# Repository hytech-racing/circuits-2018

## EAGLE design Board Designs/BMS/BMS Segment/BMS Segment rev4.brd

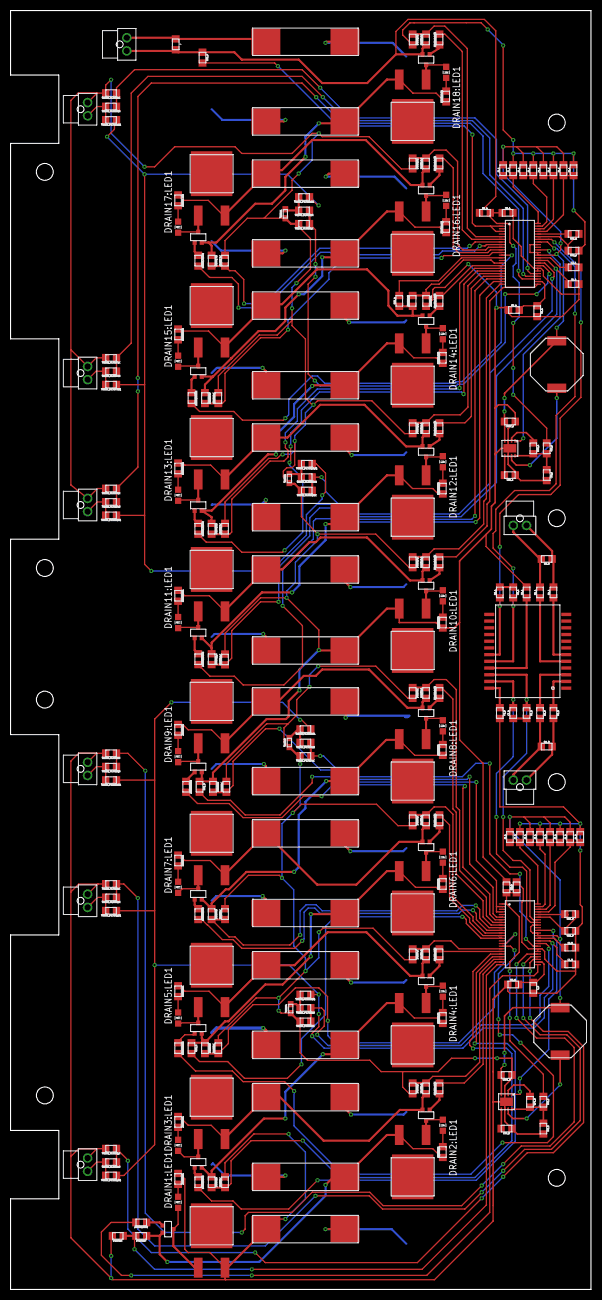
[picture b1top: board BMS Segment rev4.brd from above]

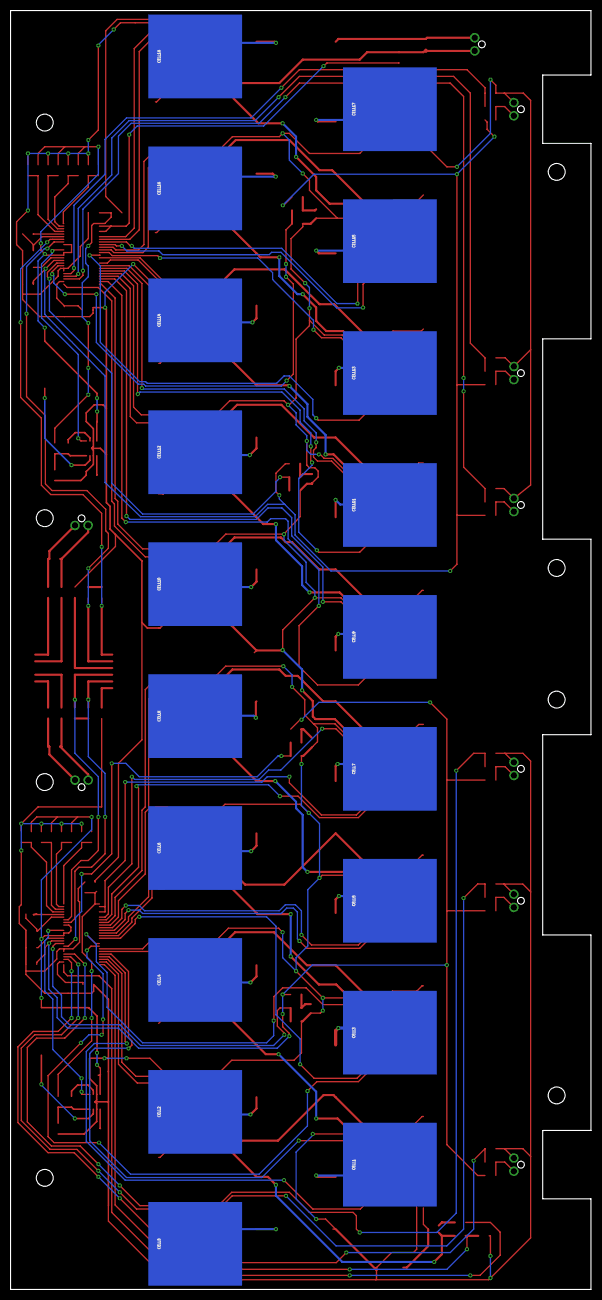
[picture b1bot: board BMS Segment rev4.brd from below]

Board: 2 copper layers, 110.0 x 242.3 mm, 273 parts (19 on the bottom side), 201 nets.

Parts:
AMS_TEST_PORT1: CONNECTOR-2NANO-FIT_VERTICAL-2; NANO-FIT_VERTICAL-2
BUCK_CONV_A: ADP2360; LFCSP-8
BUCK_CONV_B: ADP2360; LFCSP-8
C1_A, C1_B, C2_A, C2_B: 1uF; 0805
C3_A, C3_B: 15pF; 0805
C4_A, C4_B, C5_A: 10nF; 0805
C6_A, C6_B: 0.1uF; 0805
CELL0, CELL1, CELL2, CELL3, CELL4, CELL5, CELL6, CELL7, CELL8, CELL9, CELL10, CELL11, CELL12, CELL13, CELL14, CELL15, CELL16, CELL17, CELL18: BATTERY_SPRING_KEYSTONE5222; KEYSTONE5222
CIN_A: 4.7uF; 0805
CIN_B: 4.7uF; 0805
COUT_A: 22uF; 0805
COUT_B: 22uF; 0805
CSS_A: 2.2nF; 0805
CSS_B: 2.2nF; 0805
C_5: 10nF; 0805
DRAIN1:C, DRAIN2:C, DRAIN3:C, DRAIN4:C, DRAIN5:C, DRAIN6:C, DRAIN7:C, DRAIN8:C, DRAIN9:C, DRAIN10:C, DRAIN11:C, DRAIN12:C, DRAIN13:C, DRAIN14:C, DRAIN15:C, DRAIN16:C, DRAIN17:C, DRAIN18:C: 10nF; 0805
DRAIN1:DISCHARGE, DRAIN2:DISCHARGE, DRAIN3:DISCHARGE, DRAIN4:DISCHARGE, DRAIN5:DISCHARGE, DRAIN6:DISCHARGE, DRAIN7:DISCHARGE, DRAIN8:DISCHARGE, DRAIN9:DISCHARGE, DRAIN10:DISCHARGE, DRAIN11:DISCHARGE, DRAIN12:DISCHARGE, DRAIN13:DISCHARGE, DRAIN14:DISCHARGE, DRAIN15:DISCHARGE, DRAIN16:DISCHARGE, DRAIN17:DISCHARGE, DRAIN18:DISCHARGE: 5Ω; PWR163
DRAIN1:GATE, DRAIN2:GATE, DRAIN3:GATE, DRAIN4:GATE, DRAIN5:GATE, DRAIN6:GATE, DRAIN7:GATE, DRAIN8:GATE, DRAIN9:GATE, DRAIN10:GATE, DRAIN11:GATE, DRAIN12:GATE, DRAIN13:GATE, DRAIN14:GATE, DRAIN15:GATE, DRAIN16:GATE, DRAIN17:GATE, DRAIN18:GATE: 3.3kΩ; 0805
DRAIN1:LED1, DRAIN2:LED1, DRAIN3:LED1, DRAIN4:LED1, DRAIN5:LED1, DRAIN6:LED1, DRAIN7:LED1, DRAIN8:LED1, DRAIN9:LED1, DRAIN10:LED1, DRAIN11:LED1, DRAIN12:LED1, DRAIN13:LED1, DRAIN14:LED1, DRAIN15:LED1, DRAIN16:LED1, DRAIN17:LED1, DRAIN18:LED1: RED; LED-805
DRAIN1:PFET, DRAIN2:PFET, DRAIN3:PFET, DRAIN4:PFET, DRAIN5:PFET, DRAIN6:PFET, DRAIN7:PFET, DRAIN8:PFET, DRAIN9:PFET, DRAIN10:PFET, DRAIN11:PFET, DRAIN12:PFET, DRAIN13:PFET, DRAIN14:PFET, DRAIN15:PFET, DRAIN16:PFET, DRAIN17:PFET, DRAIN18:PFET: P-CHANNEL_MOSFET_DMP3099L-7; SOT23
DRAIN1:R, DRAIN2:R, DRAIN3:R, DRAIN4:R, DRAIN5:R, DRAIN6:R, DRAIN7:R, DRAIN8:R, DRAIN9:R, DRAIN10:R, DRAIN11:R, DRAIN12:R, DRAIN13:R, DRAIN14:R, DRAIN15:R, DRAIN16:R, DRAIN17:R, DRAIN18:R: 100Ω; 0805
DRAIN1:R1, DRAIN2:R1, DRAIN3:R1, DRAIN4:R1, DRAIN5:R1, DRAIN6:R1, DRAIN7:R1, DRAIN8:R1, DRAIN9:R1, DRAIN10:R1, DRAIN11:R1, DRAIN12:R1, DRAIN13:R1, DRAIN14:R1, DRAIN15:R1, DRAIN16:R1, DRAIN17:R1, DRAIN18:R1: 150; 0805
F0, F1, F2, F3, F4, F5, F6, F7, F8, F9, F10, F11, F12, F13, F14, F15, F16, F17, F18: 0001.2704.11; 5X20MM_FUSE
ISOSPI_A: CONNECTOR-2NANO-FIT_VERTICAL-2; NANO-FIT_VERTICAL-2
ISOSPI_B: CONNECTOR-2NANO-FIT_VERTICAL-2; NANO-FIT_VERTICAL-2
J, J1_A, J1_B, J2_A, J2_B, J3_A, J3_B, J4_A, J4_B, J5_A, J5_B, J6_A, J6_B, J7_A, J7_B, J8_A, J8_B: 0805
L1_A, L1_B: 330uH; SRU1048
R1_A, R1_B, R2_A, R2_B: 100Ω; 0805
R3_A, R3_B: 402Ω; 0805
R4_A, R4_B, R5_A, R5_B: 22Ω; 0805
RB1_A, RB1_B: 1.2kΩ; 0805
RB2_A, RB2_B: 800Ω; 0805
RIN_A: 1kΩ; 0805
RIN_B: 1kΩ; 0805
RM_A: 100Ω; 0805
RM_B: 100Ω; 0805
RPG_A: 10MΩ; 0805
RPG_B: 10MΩ; 0805
RU1_A, RU1_B, RU2_A, RU2_B: 100Ω; 0805
THERM1, THERM2, THERM3, THERM4: 10kΩ; 0603
THERM1A, THERM1_B: Th1; NANO-FIT_VERTICAL-2
THERM2A, THERM2_B: Th2; NANO-FIT_VERTICAL-2
THERM3A, THERM3_B: Th3; NANO-FIT_VERTICAL-2
THERM_FILTER1:C, THERM_FILTER2:C, THERM_FILTER3:C, THERM_FILTER4:C, THERM_FILTER5:C, THERM_FILTER6:C, THERM_FILTER7:C, THERM_FILTER8:C, THERM_FILTER9:C, THERM_FILTER10:C: 10nF; 0805
THERM_FILTER1:R, THERM_FILTER2:R, THERM_FILTER3:R, THERM_FILTER4:R, THERM_FILTER5:R, THERM_FILTER6:R, THERM_FILTER7:R, THERM_FILTER8:R, THERM_FILTER9:R, THERM_FILTER10:R: 100Ω; 0805
THERM_FILTER1:R1, THERM_FILTER2:R1, THERM_FILTER3:R1, THERM_FILTER4:R1, THERM_FILTER5:R1, THERM_FILTER6:R1, THERM_FILTER7:R1, THERM_FILTER8:R1, THERM_FILTER9:R1, THERM_FILTER10:R1: 10kΩ; 0805
TRANSFORMER: SM51589PEL
U$1, U$2: LTC6804-2; LTC6804

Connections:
C0_A: C5_A.1, R2_A.2, U$1.26
C0_B: C_5.1, R2_B.2, U$2.26
C1_A: DRAIN10:C.1, DRAIN10:R.2, U$1.24
C1_B: DRAIN1:C.1, DRAIN1:R.2, U$2.24
C2_A: DRAIN11:C.1, DRAIN11:R.2, U$1.22
C2_B: DRAIN2:C.1, DRAIN2:R.2, U$2.22
C3_A: DRAIN12:C.1, DRAIN12:R.2, U$1.20
C3_B: DRAIN3:C.1, DRAIN3:R.2, U$2.20
C4_A: DRAIN13:C.1, DRAIN13:R.2, U$1.18
C4_B: DRAIN4:C.1, DRAIN4:R.2, U$2.18
C5_A: DRAIN14:C.1, DRAIN14:R.2, U$1.16
C5_B: DRAIN5:C.1, DRAIN5:R.2, U$2.16
C7_A: DRAIN15:C.1, DRAIN15:R.2, U$1.12
C7_B: DRAIN6:C.1, DRAIN6:R.2, U$2.12
C8_A: DRAIN16:C.1, DRAIN16:R.2, U$1.10
C8_B: DRAIN7:C.1, DRAIN7:R.2, U$2.10
C9_A: DRAIN17:C.1, DRAIN17:R.2, U$1.8
C9_B: DRAIN8:C.1, DRAIN8:R.2, U$2.8
C10_A: DRAIN18:C.1, DRAIN18:R.2, U$1.6
C10_B: DRAIN9:C.1, DRAIN9:R.2, U$2.6
CC0: CELL0.P$1, F0.P$1
CC1: CELL1.P$1, F1.P$1
CC2: CELL2.P$1, F2.P$1
CC3: CELL3.P$1, F3.P$1
CC4: CELL4.P$1, F4.P$1
CC5: CELL5.P$1, F5.P$1
CC6: CELL6.P$1, F6.P$1
CC7: CELL7.P$1, F7.P$1
CC8: CELL8.P$1, F8.P$1
CC9: CELL9.P$1, F9.P$1
CC10: CELL10.P$1, F10.P$1
CC11: CELL11.P$1, F11.P$1
CC12: CELL12.P$1, F12.P$1
CC13: CELL13.P$1, F13.P$1
CC14: CELL14.P$1, F14.P$1
CC15: CELL15.P$1, F15.P$1
CC16: CELL16.P$1, F16.P$1
CC17: CELL17.P$1, F17.P$1
CC18: CELL18.P$1, F18.P$1
DRAIN1:GATE: DRAIN1:GATE.1, DRAIN1:PFET.1
DRAIN1:N$1: DRAIN1:DISCHARGE.1, DRAIN1:LED1.A, DRAIN1:PFET.3
DRAIN1:N$2: DRAIN1:LED1.C, DRAIN1:R1.2
DRAIN2:GATE: DRAIN2:GATE.1, DRAIN2:PFET.1
DRAIN2:N$1: DRAIN2:DISCHARGE.1, DRAIN2:LED1.A, DRAIN2:PFET.3
DRAIN2:N$2: DRAIN2:LED1.C, DRAIN2:R1.2
DRAIN3:GATE: DRAIN3:GATE.1, DRAIN3:PFET.1
DRAIN3:N$1: DRAIN3:DISCHARGE.1, DRAIN3:LED1.A, DRAIN3:PFET.3
DRAIN3:N$2: DRAIN3:LED1.C, DRAIN3:R1.2
DRAIN4:GATE: DRAIN4:GATE.1, DRAIN4:PFET.1
DRAIN4:N$1: DRAIN4:DISCHARGE.1, DRAIN4:LED1.A, DRAIN4:PFET.3
DRAIN4:N$2: DRAIN4:LED1.C, DRAIN4:R1.2
DRAIN5:GATE: DRAIN5:GATE.1, DRAIN5:PFET.1
DRAIN5:N$1: DRAIN5:DISCHARGE.1, DRAIN5:LED1.A, DRAIN5:PFET.3
DRAIN5:N$2: DRAIN5:LED1.C, DRAIN5:R1.2
DRAIN6:GATE: DRAIN6:GATE.1, DRAIN6:PFET.1
DRAIN6:N$1: DRAIN6:DISCHARGE.1, DRAIN6:LED1.A, DRAIN6:PFET.3
DRAIN6:N$2: DRAIN6:LED1.C, DRAIN6:R1.2
DRAIN7:GATE: DRAIN7:GATE.1, DRAIN7:PFET.1
DRAIN7:N$1: DRAIN7:DISCHARGE.1, DRAIN7:LED1.A, DRAIN7:PFET.3
DRAIN7:N$2: DRAIN7:LED1.C, DRAIN7:R1.2
DRAIN8:GATE: DRAIN8:GATE.1, DRAIN8:PFET.1
DRAIN8:N$1: DRAIN8:DISCHARGE.1, DRAIN8:LED1.A, DRAIN8:PFET.3
DRAIN8:N$2: DRAIN8:LED1.C, DRAIN8:R1.2
DRAIN9:GATE: DRAIN9:GATE.1, DRAIN9:PFET.1
DRAIN9:N$1: DRAIN9:DISCHARGE.1, DRAIN9:LED1.A, DRAIN9:PFET.3
DRAIN9:N$2: DRAIN9:LED1.C, DRAIN9:R1.2
DRAIN10:GATE: DRAIN10:GATE.1, DRAIN10:PFET.1
DRAIN10:N$1: DRAIN10:DISCHARGE.1, DRAIN10:LED1.A, DRAIN10:PFET.3
DRAIN10:N$2: DRAIN10:LED1.C, DRAIN10:R1.2
DRAIN11:GATE: DRAIN11:GATE.1, DRAIN11:PFET.1
DRAIN11:N$1: DRAIN11:DISCHARGE.1, DRAIN11:LED1.A, DRAIN11:PFET.3
DRAIN11:N$2: DRAIN11:LED1.C, DRAIN11:R1.2
DRAIN12:GATE: DRAIN12:GATE.1, DRAIN12:PFET.1
DRAIN12:N$1: DRAIN12:DISCHARGE.1, DRAIN12:LED1.A, DRAIN12:PFET.3
DRAIN12:N$2: DRAIN12:LED1.C, DRAIN12:R1.2
DRAIN13:GATE: DRAIN13:GATE.1, DRAIN13:PFET.1
DRAIN13:N$1: DRAIN13:DISCHARGE.1, DRAIN13:LED1.A, DRAIN13:PFET.3
DRAIN13:N$2: DRAIN13:LED1.C, DRAIN13:R1.2
DRAIN14:GATE: DRAIN14:GATE.1, DRAIN14:PFET.1
DRAIN14:N$1: DRAIN14:DISCHARGE.1, DRAIN14:LED1.A, DRAIN14:PFET.3
DRAIN14:N$2: DRAIN14:LED1.C, DRAIN14:R1.2
DRAIN15:GATE: DRAIN15:GATE.1, DRAIN15:PFET.1
DRAIN15:N$1: DRAIN15:DISCHARGE.1, DRAIN15:LED1.A, DRAIN15:PFET.3
DRAIN15:N$2: DRAIN15:LED1.C, DRAIN15:R1.2
DRAIN16:GATE: DRAIN16:GATE.1, DRAIN16:PFET.1
DRAIN16:N$1: DRAIN16:DISCHARGE.1, DRAIN16:LED1.A, DRAIN16:PFET.3
DRAIN16:N$2: DRAIN16:LED1.C, DRAIN16:R1.2
DRAIN17:GATE: DRAIN17:GATE.1, DRAIN17:PFET.1
DRAIN17:N$1: DRAIN17:DISCHARGE.1, DRAIN17:LED1.A, DRAIN17:PFET.3
DRAIN17:N$2: DRAIN17:LED1.C, DRAIN17:R1.2
DRAIN18:GATE: DRAIN18:GATE.1, DRAIN18:PFET.1
DRAIN18:N$1: DRAIN18:DISCHARGE.1, DRAIN18:LED1.A, DRAIN18:PFET.3
DRAIN18:N$2: DRAIN18:LED1.C, DRAIN18:R1.2
DRIVE_A: BUCK_CONV_A.1, U$1.38
DRIVE_B: BUCK_CONV_B.1, U$2.38
GPIO1_A: THERM_FILTER6:C.1, THERM_FILTER6:R.1, U$1.27
GPIO1_B: THERM_FILTER1:C.1, THERM_FILTER1:R.1, U$2.27
GPIO2_A: THERM_FILTER7:C.1, THERM_FILTER7:R.1, U$1.28
GPIO2_B: THERM_FILTER2:C.1, THERM_FILTER2:R.1, U$2.28
GPIO3_A: THERM_FILTER8:C.1, THERM_FILTER8:R.1, U$1.29
GPIO3_B: THERM_FILTER3:C.1, THERM_FILTER3:R.1, U$2.29
GPIO4_A: THERM_FILTER9:C.1, THERM_FILTER9:R.1, U$1.32
GPIO4_B: THERM_FILTER4:C.1, THERM_FILTER4:R.1, U$2.32
GPIO5_A: THERM_FILTER10:C.1, THERM_FILTER10:R.1, U$1.33
GPIO5_B: THERM_FILTER5:C.1, THERM_FILTER5:R.1, U$2.33
IM_A: C3_A.2, TRANSFORMER.20, U$1.41
IM_B: C3_B.2, TRANSFORMER.23, U$2.41
IP_A: R3_A.1, TRANSFORMER.19, U$1.42
IP_B: R3_B.1, TRANSFORMER.22, U$2.42
ISOSPI-M_A: ISOSPI_A.P$2, R5_A.2, RM_A.2
ISOSPI-M_B: ISOSPI_B.P$2, R5_B.2, RM_B.2
ISOSPI-P_A: ISOSPI_A.P$1, R4_A.2, RM_A.1
ISOSPI-P_B: ISOSPI_B.P$1, R4_B.2, RM_B.1
unnamed: C4_B.1, TRANSFORMER.24
unnamed: RB1_B.2, U$2.44
unnamed: THERM1_B.P$2, THERM_FILTER1:R.2, THERM_FILTER1:R1.2
unnamed: RB1_B.1, RB2_B.2, U$2.43
unnamed: R4_B.1, TRANSFORMER.3
unnamed: RB1_A.2, U$1.44
unnamed: R5_B.1, TRANSFORMER.2
unnamed: J7_B.1, J8_B.1, U$2.48
unnamed: J5_B.1, J6_B.1, U$2.47
unnamed: C3_B.1, R3_B.2
unnamed: BUCK_CONV_B.8, CIN_B.1, RIN_B.2, RPG_B.2
unnamed: BUCK_CONV_B.2, RPG_B.1
unnamed: J3_B.1, J4_B.1, U$2.46
unnamed: BUCK_CONV_B.5, CSS_B.2
unnamed: BUCK_CONV_B.7, L1_B.1
unnamed: J1_B.1, J2_B.1, U$2.45
unnamed: THERM4.2, THERM_FILTER5:R.2, THERM_FILTER5:R1.2
unnamed: THERM2_B.P$2, THERM_FILTER2:R.2, THERM_FILTER2:R1.2
unnamed: THERM3.2, THERM_FILTER4:R.2, THERM_FILTER4:R1.2
unnamed: RB1_A.1, RB2_A.2, U$1.43
unnamed: C4_A.1, TRANSFORMER.21
unnamed: R4_A.1, TRANSFORMER.6
unnamed: R5_A.1, TRANSFORMER.5
unnamed: C3_A.1, R3_A.2
unnamed: BUCK_CONV_A.8, CIN_A.1, RIN_A.2, RPG_A.2
unnamed: THERM3_B.P$2, THERM_FILTER3:R.2, THERM_FILTER3:R1.2
unnamed: BUCK_CONV_A.2, RPG_A.1
unnamed: BUCK_CONV_A.5, CSS_A.2
unnamed: BUCK_CONV_A.7, L1_A.1
unnamed: J7_A.1, J8_A.1, U$1.48
unnamed: J5_A.1, J6_A.1, U$1.47
unnamed: J3_A.1, J4_A.1, U$1.46
unnamed: J1_A.1, J2_A.1, U$1.45
unnamed: THERM1.2, THERM_FILTER9:R.2, THERM_FILTER9:R1.2
unnamed: THERM3A.P$2, THERM_FILTER8:R.2, THERM_FILTER8:R1.2
unnamed: THERM2.2, THERM_FILTER10:R.2, THERM_FILTER10:R1.2
unnamed: THERM2A.P$2, THERM_FILTER7:R.2, THERM_FILTER7:R1.2
unnamed: THERM1A.P$2, THERM_FILTER6:R.2, THERM_FILTER6:R1.2
S1_A: DRAIN10:GATE.2, U$1.25
S1_B: DRAIN1:GATE.2, U$2.25
S2_A: DRAIN11:GATE.2, U$1.23
S2_B: DRAIN2:GATE.2, U$2.23
S3_A: DRAIN12:GATE.2, U$1.21
S3_B: DRAIN3:GATE.2, U$2.21
S4_A: DRAIN13:GATE.2, U$1.19
S4_B: DRAIN4:GATE.2, U$2.19
S5_A: DRAIN14:GATE.2, U$1.17
S5_B: DRAIN5:GATE.2, U$2.17
S7_A: DRAIN15:GATE.2, U$1.13
S7_B: DRAIN6:GATE.2, U$2.13
S8_A: DRAIN16:GATE.2, U$1.11
S8_B: DRAIN7:GATE.2, U$2.11
S9_A: DRAIN17:GATE.2, U$1.9
S9_B: DRAIN8:GATE.2, U$2.9
S10_A: DRAIN18:GATE.2, U$1.7
S10_B: DRAIN9:GATE.2, U$2.7
SENSE1: DRAIN1:PFET.2, DRAIN1:R.1, DRAIN2:DISCHARGE.2, DRAIN2:R1.1, F1.P$2
SENSE2: DRAIN2:PFET.2, DRAIN2:R.1, DRAIN3:DISCHARGE.2, DRAIN3:R1.1, F2.P$2
SENSE3: DRAIN3:PFET.2, DRAIN3:R.1, DRAIN4:DISCHARGE.2, DRAIN4:R1.1, F3.P$2
SENSE4: DRAIN4:PFET.2, DRAIN4:R.1, DRAIN5:DISCHARGE.2, DRAIN5:R1.1, F4.P$2
SENSE5: DRAIN5:PFET.2, DRAIN5:R.1, DRAIN6:DISCHARGE.2, DRAIN6:R1.1, F5.P$2, RU2_B.1
SENSE6: DRAIN6:PFET.2, DRAIN6:R.1, DRAIN7:DISCHARGE.2, DRAIN7:R1.1, F6.P$2
SENSE7: DRAIN7:PFET.2, DRAIN7:R.1, DRAIN8:DISCHARGE.2, DRAIN8:R1.1, F7.P$2
SENSE8: DRAIN8:PFET.2, DRAIN8:R.1, DRAIN9:DISCHARGE.2, DRAIN9:R1.1, F8.P$2
SENSE10: DRAIN10:PFET.2, DRAIN10:R.1, DRAIN11:DISCHARGE.2, DRAIN11:R1.1, F10.P$2
SENSE11: DRAIN11:PFET.2, DRAIN11:R.1, DRAIN12:DISCHARGE.2, DRAIN12:R1.1, F11.P$2
SENSE12: DRAIN12:PFET.2, DRAIN12:R.1, DRAIN13:DISCHARGE.2, DRAIN13:R1.1, F12.P$2
SENSE13: DRAIN13:PFET.2, DRAIN13:R.1, DRAIN14:DISCHARGE.2, DRAIN14:R1.1, F13.P$2
SENSE14: DRAIN14:PFET.2, DRAIN14:R.1, DRAIN15:DISCHARGE.2, DRAIN15:R1.1, F14.P$2, RU2_A.1
SENSE15: DRAIN15:PFET.2, DRAIN15:R.1, DRAIN16:DISCHARGE.2, DRAIN16:R1.1, F15.P$2
SENSE16: DRAIN16:PFET.2, DRAIN16:R.1, DRAIN17:DISCHARGE.2, DRAIN17:R1.1, F16.P$2
SENSE17: DRAIN17:PFET.2, DRAIN17:R.1, DRAIN18:DISCHARGE.2, DRAIN18:R1.1, F17.P$2
SENSE18: AMS_TEST_PORT1.P$2, DRAIN18:PFET.2, DRAIN18:R.1, J.2, R1_A.1, RU1_A.1
SENSE18_J: AMS_TEST_PORT1.P$1, F18.P$2, J.1
UNUSED1_A: RU1_A.2, U$1.2, U$1.4
UNUSED1_B: RU1_B.2, U$2.2, U$2.4
UNUSED2_A: RU2_A.2, U$1.14
UNUSED2_B: RU2_B.2, U$2.14
V+_A: C6_A.1, R1_A.2, RIN_A.1, U$1.1
V+_B: C6_B.1, R1_B.2, RIN_B.1, U$2.1
V-_A: BUCK_CONV_A.3, BUCK_CONV_A.6, BUCK_CONV_A.PAD, C1_A.2, C2_A.2, C4_A.2, C5_A.2, C6_A.2, CIN_A.2, COUT_A.1, CSS_A.1, DRAIN9:PFET.2, DRAIN9:R.1, DRAIN10:C.2, DRAIN10:DISCHARGE.2, DRAIN10:R1.1, DRAIN11:C.2, DRAIN12:C.2, DRAIN13:C.2, DRAIN14:C.2, DRAIN15:C.2, DRAIN16:C.2, DRAIN17:C.2, DRAIN18:C.2, F9.P$2, J1_A.2, J3_A.2, J5_A.2, J7_A.2, R1_B.1, R2_A.1, RB2_A.1, RU1_B.1, THERM1.1, THERM1A.P$1, THERM2.1, THERM2A.P$1, THERM3A.P$1, THERM_FILTER6:C.2, THERM_FILTER7:C.2, THERM_FILTER8:C.2, THERM_FILTER9:C.2, THERM_FILTER10:C.2, U$1.30, U$1.31
V-_B: BUCK_CONV_B.3, BUCK_CONV_B.6, BUCK_CONV_B.PAD, C1_B.2, C2_B.2, C4_B.2, C6_B.2, CIN_B.2, COUT_B.1, CSS_B.1, C_5.2, DRAIN1:C.2, DRAIN1:DISCHARGE.2, DRAIN1:R1.1, DRAIN2:C.2, DRAIN3:C.2, DRAIN4:C.2, DRAIN5:C.2, DRAIN6:C.2, DRAIN7:C.2, DRAIN8:C.2, DRAIN9:C.2, F0.P$2, J1_B.2, J3_B.2, J5_B.2, J7_B.2, R2_B.1, RB2_B.1, THERM1_B.P$1, THERM2_B.P$1, THERM3.1, THERM3_B.P$1, THERM4.1, THERM_FILTER1:C.2, THERM_FILTER2:C.2, THERM_FILTER3:C.2, THERM_FILTER4:C.2, THERM_FILTER5:C.2, U$2.30, U$2.31
VREF1_A: C2_A.1, U$1.35
VREF1_B: C2_B.1, U$2.35
VREF2_A: C1_A.1, THERM_FILTER6:R1.1, THERM_FILTER7:R1.1, THERM_FILTER8:R1.1, THERM_FILTER9:R1.1, THERM_FILTER10:R1.1, U$1.34
VREF2_B: C1_B.1, THERM_FILTER1:R1.1, THERM_FILTER2:R1.1, THERM_FILTER3:R1.1, THERM_FILTER4:R1.1, THERM_FILTER5:R1.1, U$2.34
VREG_A: BUCK_CONV_A.4, COUT_A.2, J2_A.2, J4_A.2, J6_A.2, J8_A.2, L1_A.2, U$1.36, U$1.37, U$1.40
VREG_B: BUCK_CONV_B.4, COUT_B.2, J2_B.2, J4_B.2, J6_B.2, J8_B.2, L1_B.2, U$2.36, U$2.37, U$2.40

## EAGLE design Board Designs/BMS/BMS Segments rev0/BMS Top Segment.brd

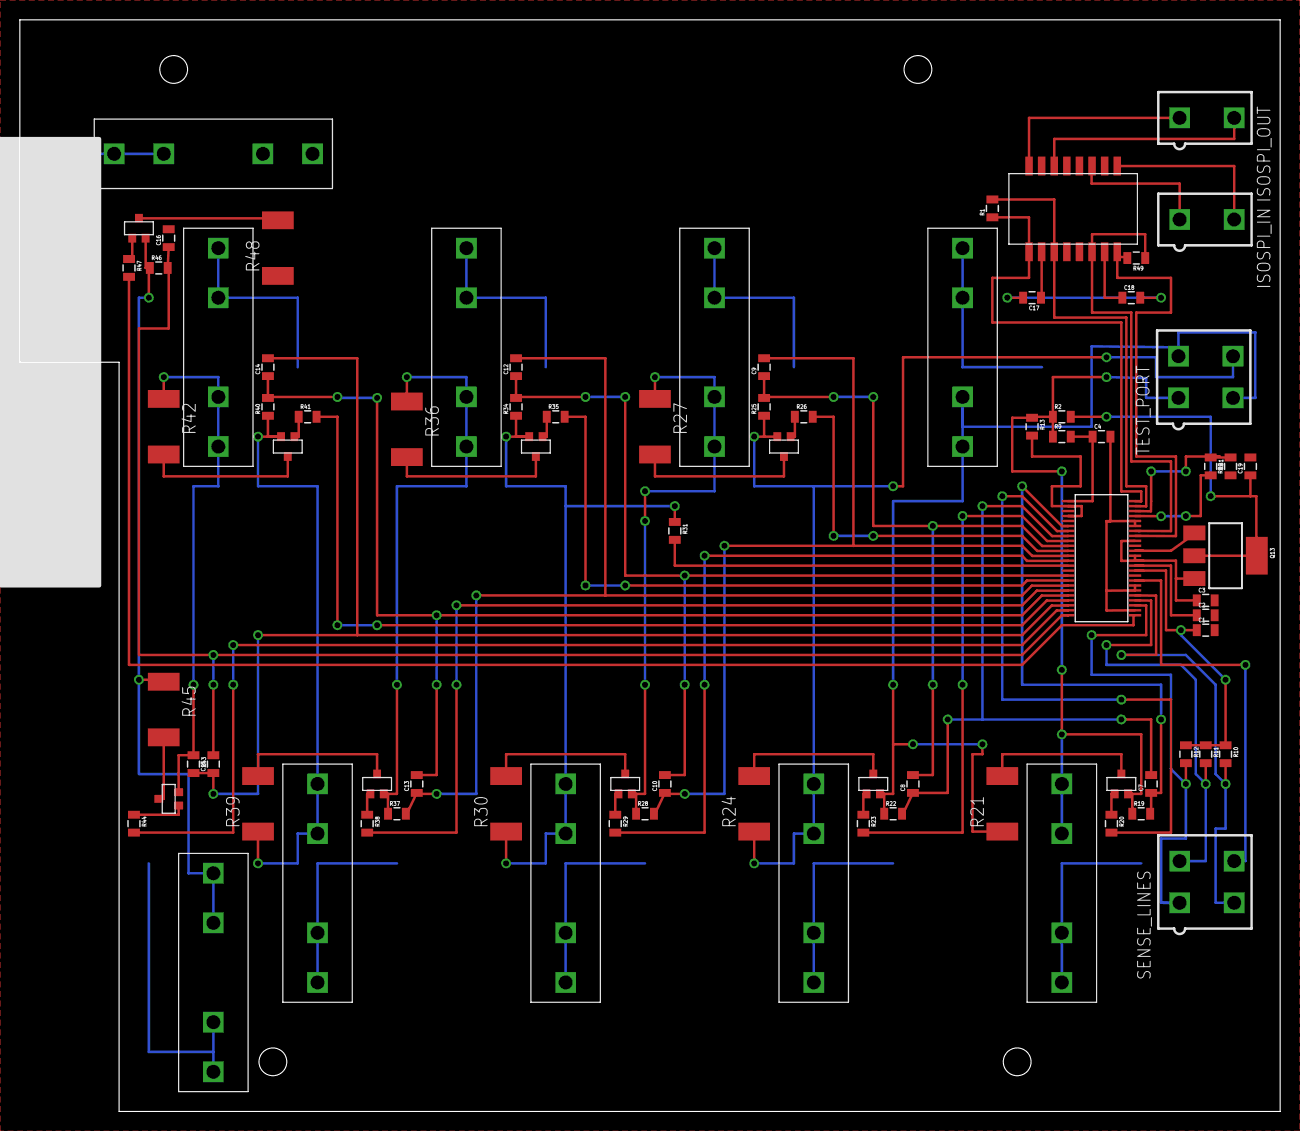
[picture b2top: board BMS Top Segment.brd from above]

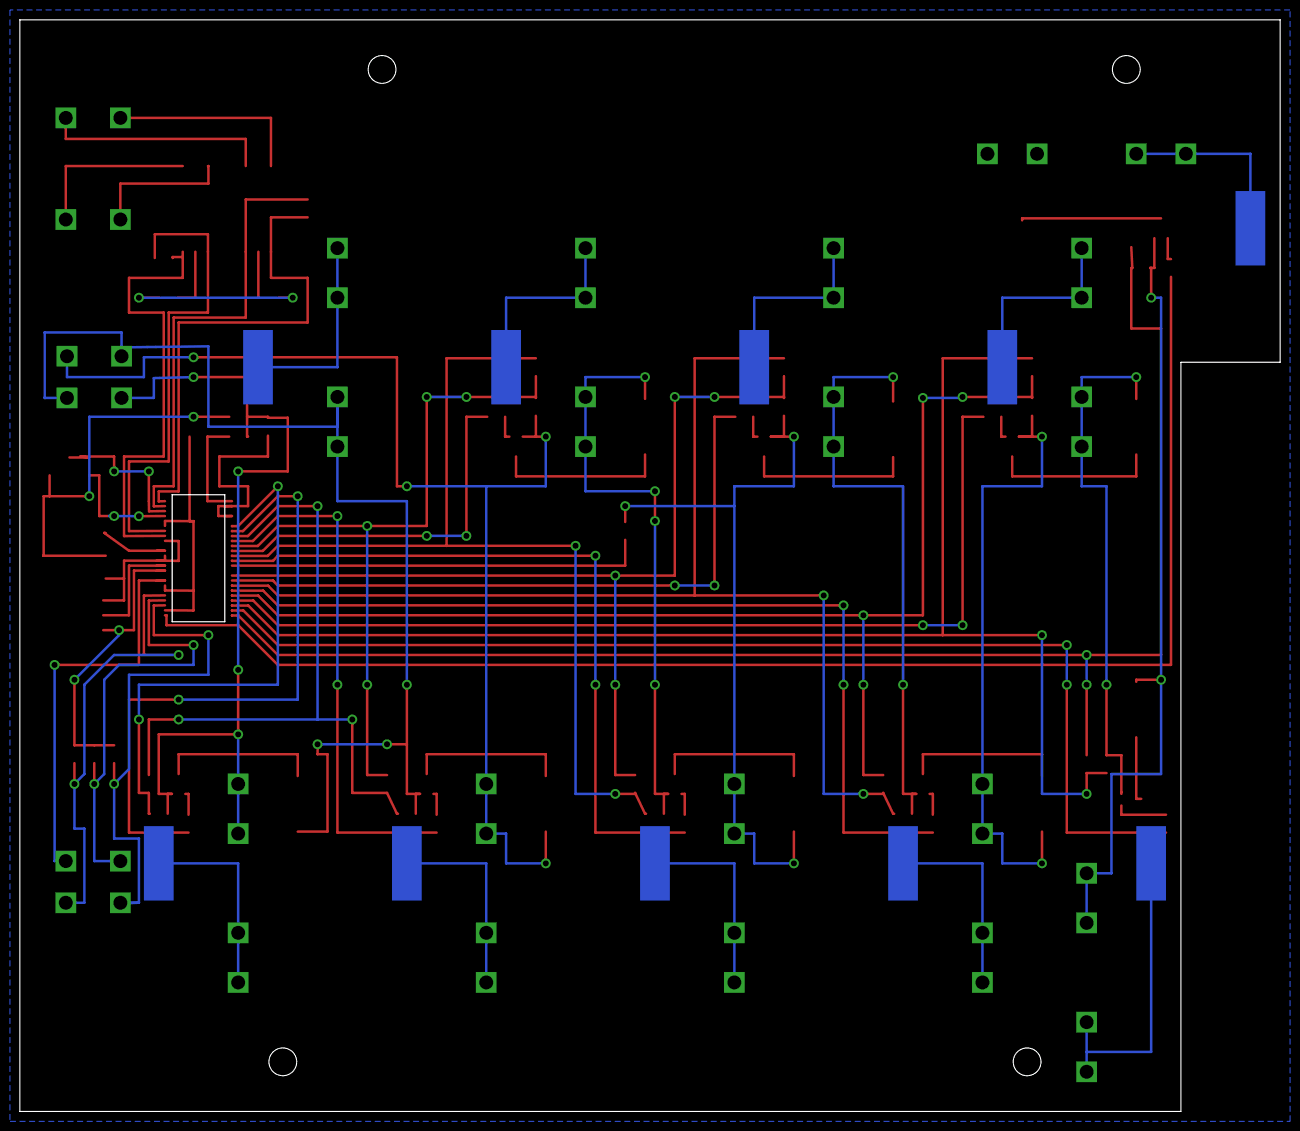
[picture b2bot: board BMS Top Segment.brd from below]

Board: 2 copper layers, 127.0 x 110.0 mm, 90 parts (10 on the bottom side), 80 nets.

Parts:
C1, C2, C3: 1uF; 0805
C4, C19: 0.1uF; 0805
C7, C8, C9, C10, C12, C13, C14, C15, C16: 10nF; 0805
C17, C18: 100pF; 0805
CONTACT1, CONTACT2, CONTACT3, CONTACT4, CONTACT5, CONTACT6, CONTACT7, CONTACT8, CONTACT9, CONTACT10: S1791-42R
F1, F2, F3, F4, F5, F6, F7, F8, F9, F10: 0751.0110
ISOSPI_IN: MINIFIT_5566-2
ISOSPI_OUT: MINIFIT_5566-2
Q3, Q4, Q5, Q6, Q8, Q9, Q10, Q11, Q12: P-CHANNEL_MOSFET_DMP3099L-7; SOT23
Q13: NPN_BCP56T1; SOT223
R1, R49: 120Ω; 0805
R2, R9, R13, R19, R22, R25, R28, R31, R34, R37, R40, R43, R46: 100Ω; 0805
R10, R11, R12: 10kΩ; 0805
R20, R23, R26, R29, R35, R38, R41, R44, R47: 3.3kΩ; 0805
R21, R24, R27, R30, R36, R39, R42, R45, R48: 33Ω; R2512
RB1, RB2: 0805
SENSE_LINES: MINIFIT_5566-4
TEST_PORT: MINIFIT_5566-4
TRANSFORMER-: 350uH; 749010013
U$2: LTC6804

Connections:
C1: C15.2, C16.1, R46.2, U$2.24
C2: C14.2, C15.1, R43.2, U$2.22
C3: C13.2, C14.1, R40.2, U$2.20
C4: C12.2, C13.1, R37.2, U$2.18
C5: C10.2, C12.1, R34.2, U$2.16
C7: C9.2, C10.1, R28.2, U$2.12
C8: C8.2, C9.1, R25.2, U$2.10
C9: C7.2, C8.1, R22.2, U$2.8
C10: C7.1, R19.2, U$2.6
CELL1: F1.R1, F1.R2, Q3.2, R2.1, R9.1, R13.1, R19.1, TEST_PORT.1
CELL2: F2.R1, F2.R2, Q4.2, R21.1, R22.1, TEST_PORT.2, TEST_PORT.3
CELL3: F3.R1, F3.R2, Q5.2, R24.1, R25.1, TEST_PORT.4
CELL4: F4.R1, F4.R2, Q6.2, R27.1, R28.1
CELL5: F5.R1, F5.R2, Q8.2, R30.1, R31.1, R34.1
CELL6: F6.R1, F6.R2, Q9.2, R36.1, R37.1
CELL7: F7.R1, F7.R2, Q10.2, R39.1, R40.1
CELL8: F8.R1, F8.R2, Q11.2, R42.1, R43.1
CELL9: F9.R1, F9.R2, Q12.2, R45.1, R46.1
CURRENT_SENSE: SENSE_LINES.4, U$2.32
DRIVE: Q13.1, U$2.38
GND: C1.2, C2.2, C3.2, C4.2, C16.2, C17.2, C18.2, C19.2, F10.R1, F10.R2, R48.1, RB2.1, U$2.26, U$2.30, U$2.31, U$2.43, U$2.44
ISOSPI-M_IN: ISOSPI_IN.2, TRANSFORMER-.8
ISOSPI-M_OUT: ISOSPI_OUT.2, TRANSFORMER-.3
ISOSPI-P_IN: ISOSPI_IN.1, TRANSFORMER-.6
ISOSPI-P_OUT: ISOSPI_OUT.1, TRANSFORMER-.1
unnamed: C18.1, TRANSFORMER-.10
unnamed: C17.1, TRANSFORMER-.15
unnamed: RB1.2, U$2.45
unnamed: R1.1, TRANSFORMER-.16, U$2.48
unnamed: RB1.1, RB2.2, U$2.46
unnamed: R49.1, TRANSFORMER-.11, U$2.42
unnamed: R49.2, TRANSFORMER-.9, U$2.41
unnamed: CONTACT1.P$1, F1.L1, F1.L2
unnamed: Q3.1, R20.1
unnamed: CONTACT2.P$1, F2.L1, F2.L2
unnamed: CONTACT3.P$1, F3.L1, F3.L2
unnamed: Q3.3, R21.2
unnamed: CONTACT4.P$1, F4.L1, F4.L2
unnamed: Q8.1, R35.1
unnamed: Q9.1, R38.1
unnamed: CONTACT5.P$1, F5.L1, F5.L2
unnamed: CONTACT6.P$1, F6.L1, F6.L2
unnamed: Q4.3, R24.2
unnamed: CONTACT7.P$1, F7.L1, F7.L2
unnamed: Q10.1, R41.1
unnamed: Q11.1, R44.1
unnamed: Q12.1, R47.1
unnamed: Q5.3, R27.2
unnamed: CONTACT8.P$1, F8.L1, F8.L2
unnamed: CONTACT9.P$1, F9.L1, F9.L2
unnamed: CONTACT10.P$1, F10.L1, F10.L2
unnamed: Q6.3, R30.2
unnamed: R1.2, TRANSFORMER-.14, U$2.47
unnamed: Q8.3, R36.2
unnamed: Q9.3, R39.2
unnamed: Q10.3, R42.2
unnamed: Q11.3, R45.2
unnamed: Q12.3, R48.2
unnamed: Q4.1, R23.1
unnamed: Q5.1, R26.1
unnamed: Q6.1, R29.1
S1: R47.2, U$2.25
S2: R44.2, U$2.23
S3: R41.2, U$2.21
S4: R38.2, U$2.19
S5: R35.2, U$2.17
S7: R29.2, U$2.13
S8: R26.2, U$2.11
S9: R23.2, U$2.9
S10: R20.2, U$2.7
SUPPLY: C19.1, Q13.2, Q13.4, R2.2
THERMISTOR1: R12.2, SENSE_LINES.1, U$2.27
THERMISTOR2: R11.2, SENSE_LINES.2, U$2.28
THERMISTOR3: R10.2, SENSE_LINES.3, U$2.29
UNUSED_CELL_LINES_1: R13.2, U$2.2, U$2.4
UNUSED_CELL_LINES_2: R31.2, U$2.14
V+: C4.1, R9.2, U$2.1
VREF1: C2.1, U$2.35
VREF2: C1.1, R10.1, R11.1, R12.1, U$2.34
VREG: C3.1, Q13.3, U$2.36, U$2.37, U$2.40

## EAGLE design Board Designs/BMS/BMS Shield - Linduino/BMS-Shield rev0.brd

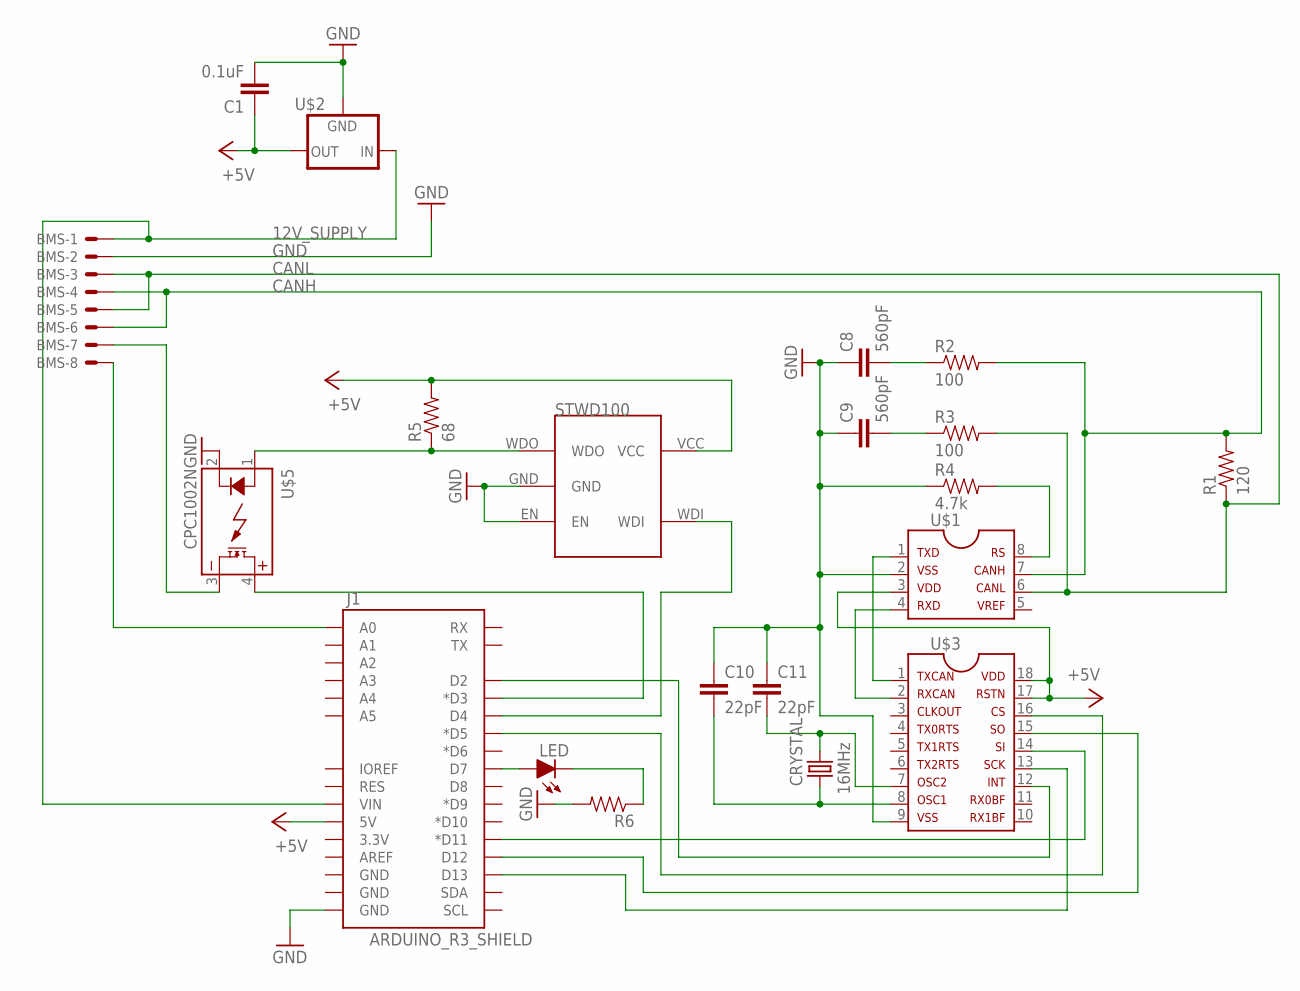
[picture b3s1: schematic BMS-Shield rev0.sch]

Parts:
BMS: MINIFIT_5566-8
C1: 0.1uF; 0805@1
C8, C9: 560pF; 0805@1
C10, C11: 22pF; 0805@1
CRYSTAL: 16MHz; HC49UP
J1: ARDUINO_R3_SHIELD; UNO_R3_SHIELD
LED: LED-0805; LED-805
R1: 120; 0805
R2, R3: 100; 0805
R4: 4.7k; 0805
R5: 68; 0805
R6: RESISTOR0805-RES; 0805
U$1: MCP2551; SOIC-08
U$2: 5VREG_LM340-NLM340MPX-5.0/NOPB; SOT223
U$3: MCP2515SMD; SOIC-18W
U$4: STWD100; SOT23-5
U$5: CPC1002N; SOP04

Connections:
12V_SUPPLY: BMS.1, J1.VIN, U$2.1 (IN)
+5V: C1.1, J1.5V, R5.2, U$1.3, U$2.3 (OUT), U$3.17, U$3.18, U$4.VCC
CANH: BMS.4, BMS.6, R1.2, R2.2, U$1.7
CANL: BMS.3, BMS.5, R1.1, R3.2, U$1.6
CS: J1.D5 (*D5), U$3.16
GND: BMS.2, C1.2, C8.1, C9.1, C10.1, C11.1, J1.GND@0 (GND), R4.1, R6.2, U$1.2, U$2.2 (GND), U$2.4 (GND), U$3.9, U$4.EN, U$4.GND, U$5.2 (CONTROL-)
unnamed: BMS.8, J1.A0
unnamed: J1.D12, U$3.15
unnamed: J1.D11 (*D11), U$3.14
unnamed: J1.D13, U$3.13
unnamed: R5.1, U$4.WDO, U$5.1 (CONTROL+)
unnamed: J1.D4, U$4.WDI
unnamed: J1.D7, LED.A
unnamed: BMS.7, U$5.3 (DC-)
unnamed: J1.D3 (*D3), U$5.4 (DC+)
unnamed: J1.D2, U$3.12
unnamed: C10.2, CRYSTAL.2, U$3.8
unnamed: U$1.1, U$3.1
unnamed: U$1.4, U$3.2
unnamed: C8.2, R2.1
unnamed: C11.2, CRYSTAL.1, U$3.7
unnamed: R4.2, U$1.8
unnamed: C9.2, R3.1
unnamed: LED.C, R6.1

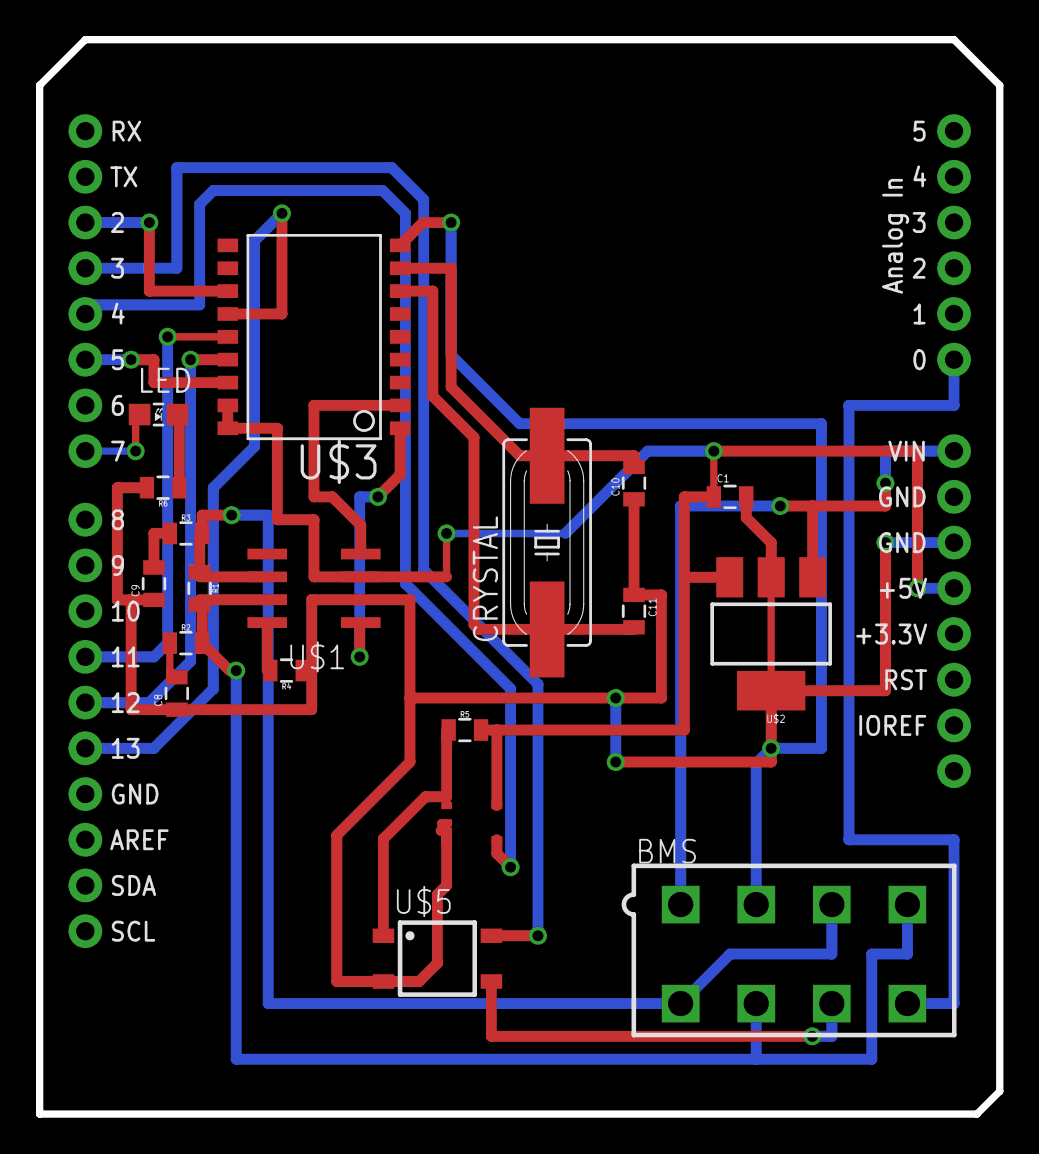
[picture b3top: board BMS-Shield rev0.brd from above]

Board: 2 copper layers, 53.3 x 59.7 mm, 20 parts (0 on the bottom side), 24 nets.

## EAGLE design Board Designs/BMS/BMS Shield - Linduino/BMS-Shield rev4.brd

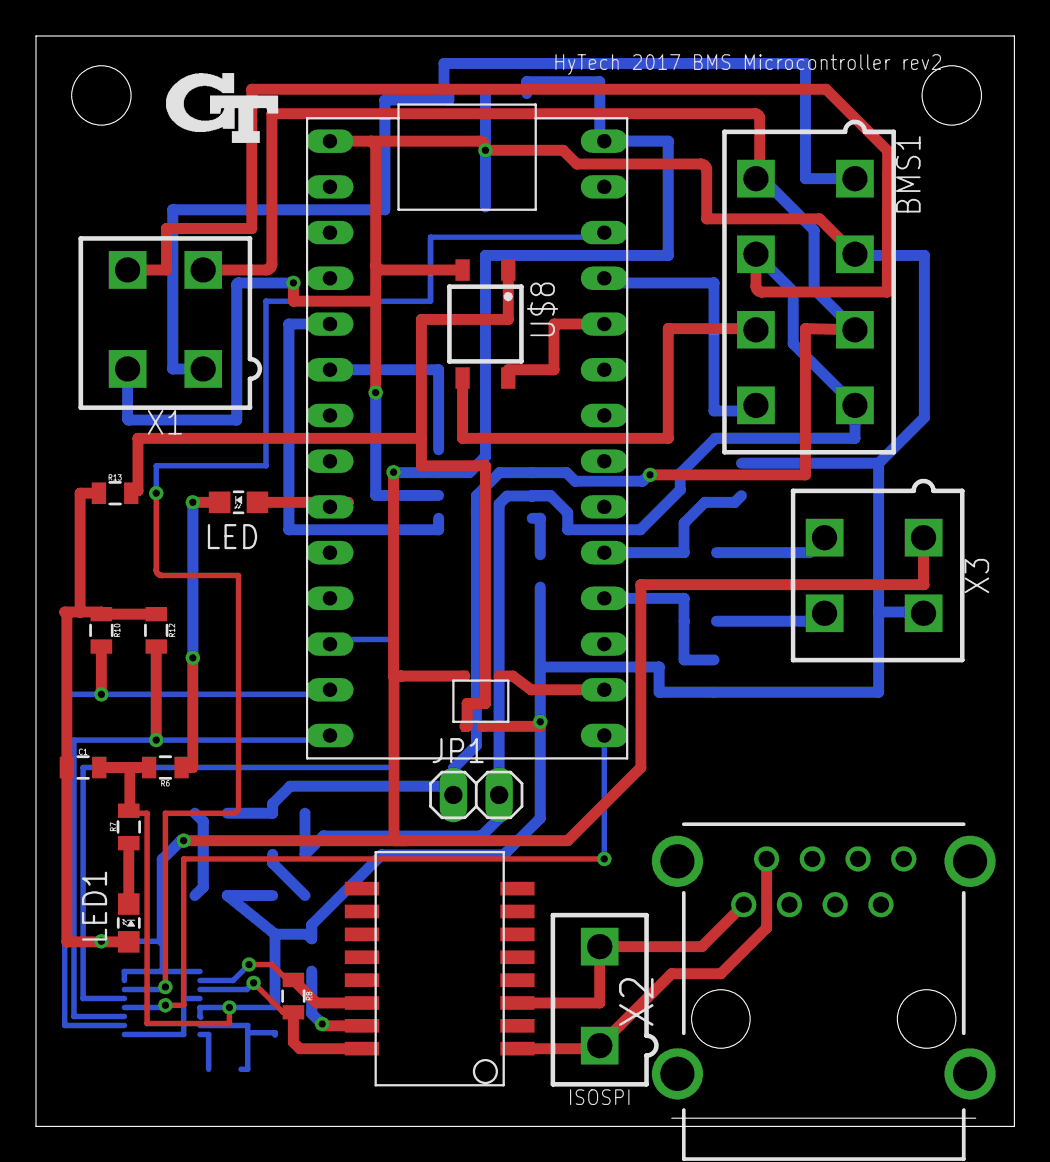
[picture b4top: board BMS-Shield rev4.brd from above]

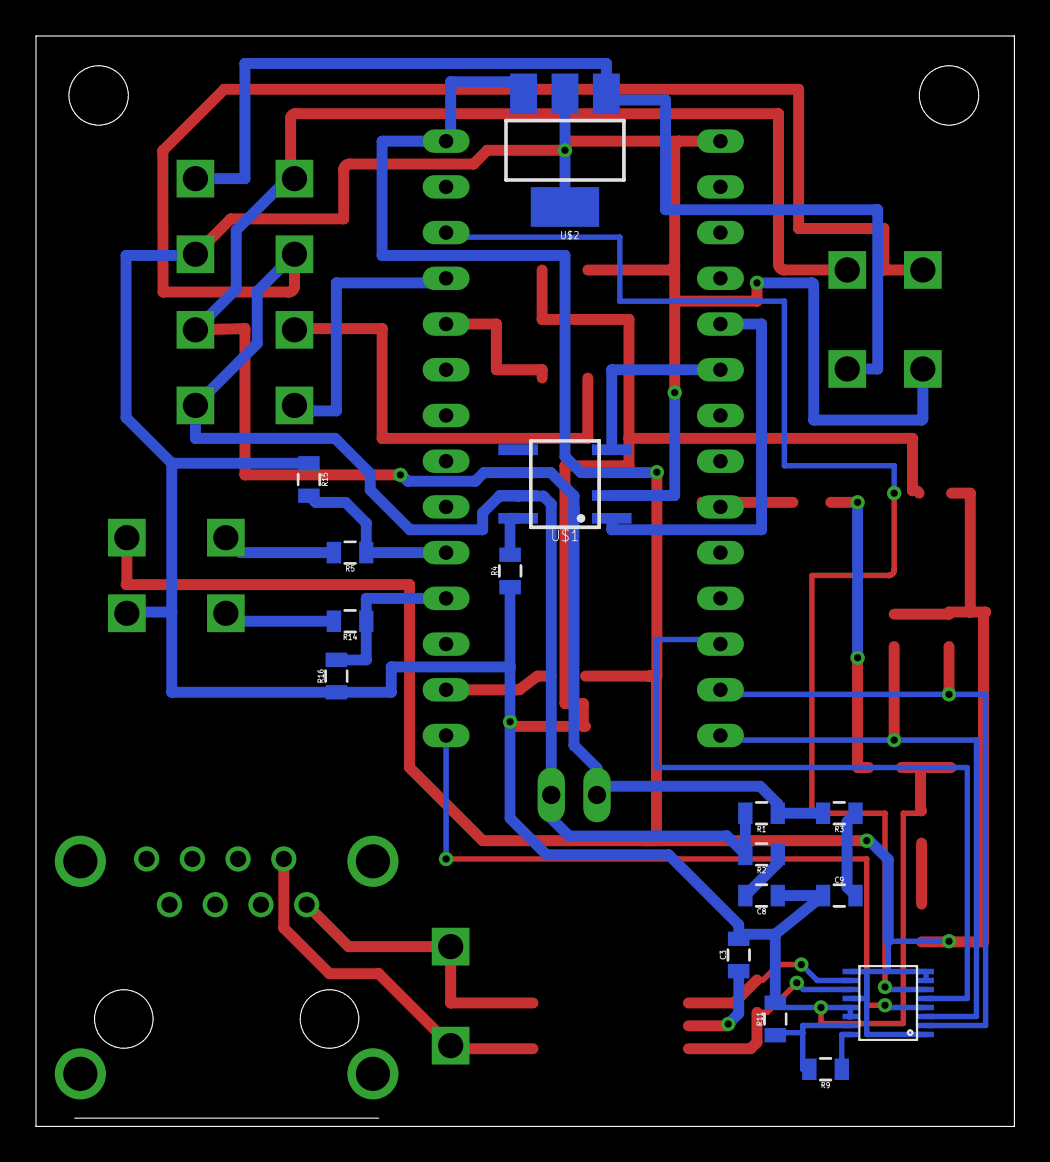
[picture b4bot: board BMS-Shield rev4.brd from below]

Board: 2 copper layers, 54.3 x 60.6 mm, 35 parts (16 on the bottom side), 34 nets.

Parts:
BMS1: MINIFIT_5566-8
C1: 0.1uF; 0805
C3: 27pF; 0805
C8, C9: 560pF; 0805
ISOSPI: CONNECTOR-2; MINIFIT_5566-2
JP1: M02; 1X02
LED, LED1: LED-805
R1, R8: 120; 0805
R2, R3: 100; 0805
R4, R5, R9, R11, R14: 1k; 0805
R6, R7: 0805
R10, R12, R15, R16: 2k; 0805
R13: 68; 0805
U$1: MCP2551; SOIC-08
U$2: SOT223
U$3: STWD100; SOT23-5
U$6: LTC6820; MSOP-16
U$7: TEENSY_3.2_SIMPLE
U$8: CPC1002N; SOP04
U$15: HX1188NLHX1188NL; HX1188NL
X1, X3: CONNECTOR-4; MINIFIT_5566-4
X2: RJ45-6L21-B; RJ45-SHIELD1

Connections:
12V_SUPPLY: BMS1.1, U$2.1, X1.1
+5V: C1.1, LED1.A, R10.1, R12.1, R13.1, U$1.3, U$2.3, U$3.VCC, U$6.1, U$6.7, U$6.8, U$6.9, U$6.12, U$7.VIN, X3.1
CANH: BMS1.4, BMS1.6, JP1.2, R1.2, R2.2, U$1.7, X1.4
CANL: BMS1.3, BMS1.5, JP1.1, R1.1, R3.2, U$1.6, X1.3
GND: BMS1.2, C1.2, C3.2, C8.1, C9.1, R4.1, R6.2, R7.2, R11.2, R15.1, R16.1, U$1.2, U$2.2, U$2.4, U$3.EN, U$3.GND, U$6.13, U$6.14, U$7.GND, U$8.2, X1.2, X3.2
ISOSPI-M: ISOSPI.2, U$15.3, X2.1
ISOSPI-P: ISOSPI.1, U$15.1, X2.2
MISO: R12.2, U$6.3, U$7.D12
MOSI: R10.2, U$6.2, U$7.D11
unnamed: R5.2, X3.3
unnamed: U$1.4, U$7.D4(CANRX)
unnamed: LED.A, U$7.D7(RX3)
unnamed: U$6.6, U$7.3.3V
unnamed: R5.1, R15.2, U$7.A3
unnamed: R14.2, X3.4
unnamed: BMS1.7, U$8.3
unnamed: R14.1, R16.2, U$7.A2
unnamed: U$3.WDI, U$7.A0
unnamed: R13.2, U$3.WDO, U$8.1
unnamed: U$7.A8, U$8.4
unnamed: U$1.1, U$7.D3(CANTX)
unnamed: BMS1.8, U$7.A9
unnamed: C8.2, R2.1
unnamed: U$6.5, U$7.D10(TX2)
unnamed: R4.2, U$1.8
unnamed: C9.2, R3.1
unnamed: LED.C, R6.1
unnamed: LED1.C, R7.1
unnamed: R9.1, U$6.16
unnamed: R9.2, R11.1, U$6.15
unnamed: R8.1, U$6.10, U$15.14
unnamed: R8.2, U$6.11, U$15.16
unnamed: C3.1, U$15.15
SCK: U$6.4, U$7.D13

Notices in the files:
parts and their libraries:
SparkFun-FreqCtrl: Licensing: Creative Commons ShareAlike 4.0 International - https://creativecommons.org/licenses/by-sa/4.0
